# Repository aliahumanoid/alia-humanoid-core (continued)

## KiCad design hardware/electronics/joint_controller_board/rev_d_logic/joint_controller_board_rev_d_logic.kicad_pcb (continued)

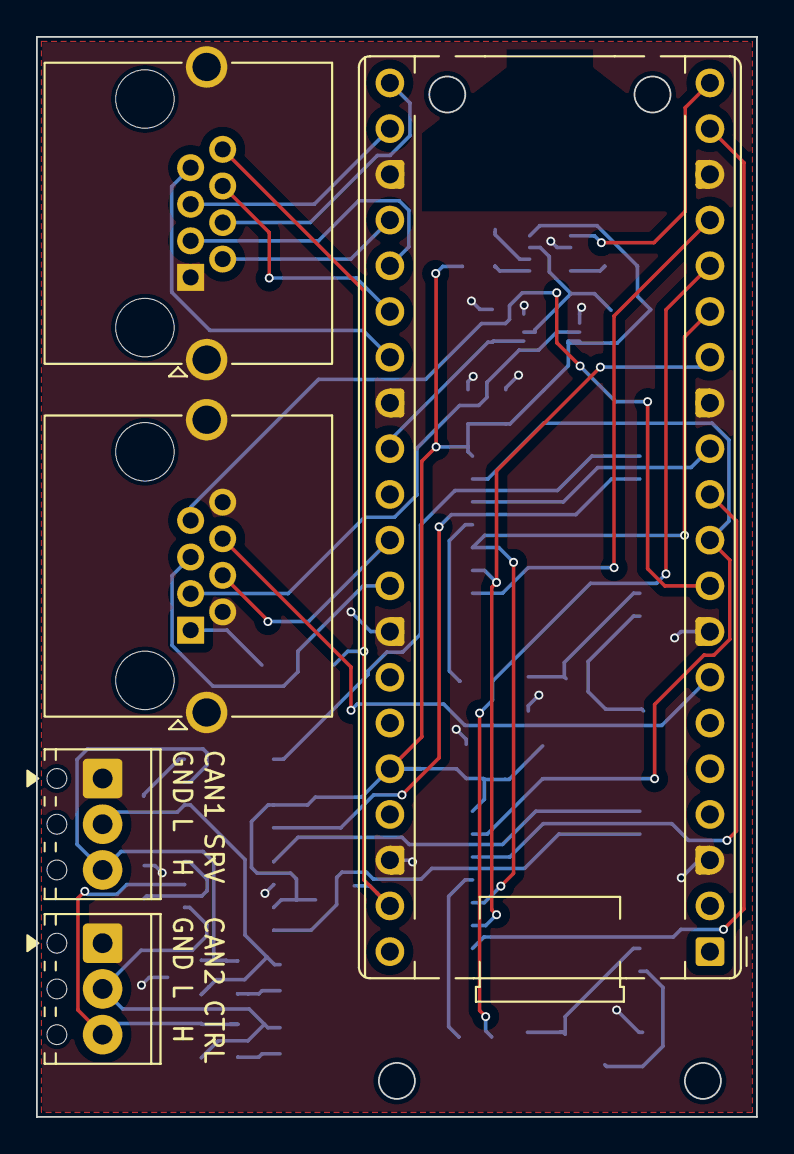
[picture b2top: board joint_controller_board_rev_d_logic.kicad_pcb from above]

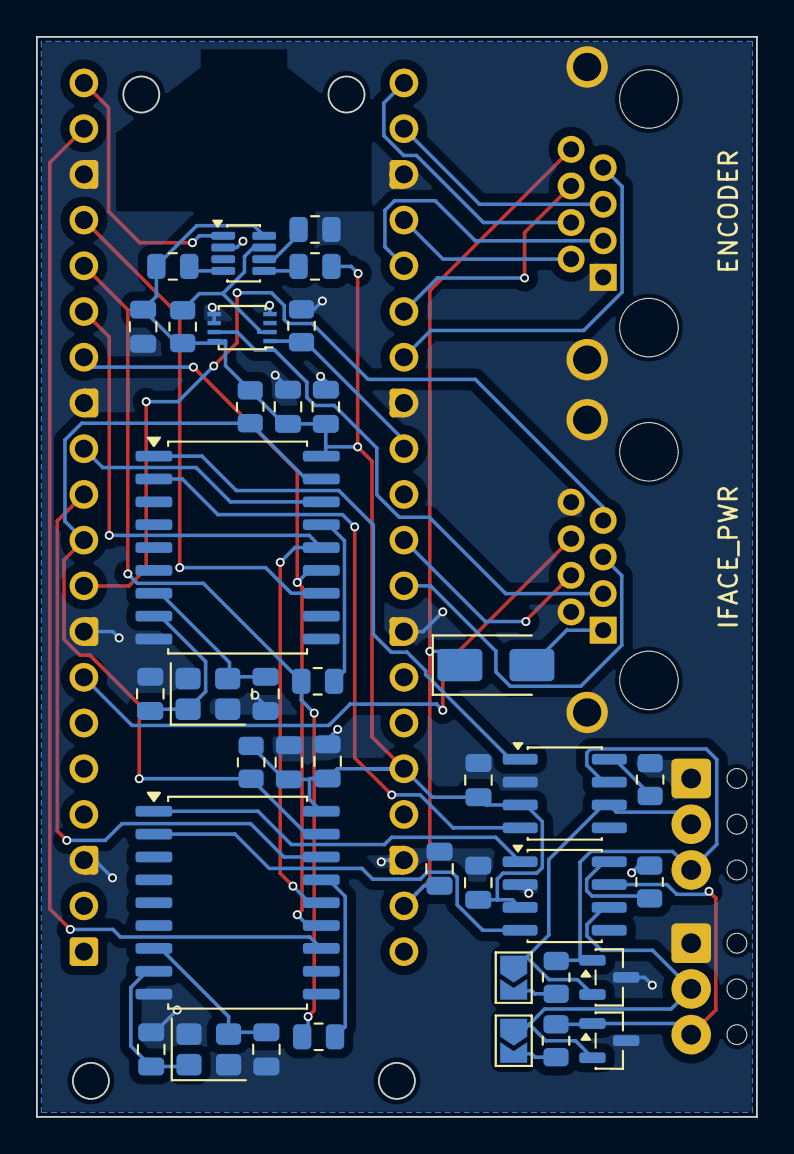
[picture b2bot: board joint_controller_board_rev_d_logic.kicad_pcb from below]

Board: 2 copper layers, 40.0 x 60.0 mm, 43 parts (38 on the bottom side), 47 nets.

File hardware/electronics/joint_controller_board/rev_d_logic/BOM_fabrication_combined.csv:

Designator,Footprint,Quantity,Manufacturer Part Number,Manufacturer,Description,Assembly_Type,Populate,Sourcing,Notes
U_CAN1,SOIC-18W_7.5x11.6mm_P1.27mm,1,MCP2515-E/SO,Microchip,Stand-alone CAN controller with SPI interface,SMD,YES,LCSC / preferred source,CAN1 controller
U_CAN2,SOIC-18W_7.5x11.6mm_P1.27mm,1,MCP2515-E/SO,Microchip,Stand-alone CAN controller with SPI interface,SMD,YES,LCSC / preferred source,CAN2 controller
U_TRX1,SOIC-8_3.9x4.9mm_P1.27mm,1,SN65HVD230DR,Texas Instruments,3.3V CAN transceiver,SMD,YES,LCSC / preferred source,CAN1 transceiver
U_TRX2,SOIC-8_3.9x4.9mm_P1.27mm,1,SN65HVD230DR,Texas Instruments,3.3V CAN transceiver,SMD,YES,LCSC / preferred source,CAN2 transceiver
U_WDT1,SOT-23-8,1,MAX6369KA+T,Analog Devices / Maxim,Pin-selectable watchdog timer,SMD,YES,LCSC / preferred source,Hardware watchdog
U4,VSSOP-8_2.4x2.1mm_P0.5mm,1,SN74LVC2G08DCUR,Texas Instruments,Dual AND gate 1.65V to 5.5V,SMD,YES,LCSC / preferred source,Safety gating logic
D1,SOT-23,1,PESD2CAN24XLT-Q,Nexperia,Automotive CAN ESD protection diode,SMD,YES,LCSC / preferred source,CAN1 TVS
D2,SOT-23,1,PESD2CAN24XLT-Q,Nexperia,Automotive CAN ESD protection diode,SMD,YES,LCSC / preferred source,CAN2 TVS
D_PWR1,D_SMA,1,SS24,Multiple,Schottky diode 2A 40V SMA,SMD,YES,LCSC / preferred source,5V input OR-ing / reverse backfeed protection
Y1,Crystal_SMD_3225-4Pin_3.2x2.5mm,1,3225 8M 12PF 10PPM,SOSET / Equivalent,8MHz SMD crystal 3225-4P,SMD,YES,LCSC / preferred source,CAN1 clock crystal
Y2,Crystal_SMD_3225-4Pin_3.2x2.5mm,1,3225 8M 12PF 10PPM,SOSET / Equivalent,8MHz SMD crystal 3225-4P,SMD,YES,LCSC / preferred source,CAN2 clock crystal
C2,C_0805_2012Metric,1,CL21B104KBCNNNC,Samsung,100nF 50V X7R 0805 capacitor,SMD,YES,LCSC / preferred source,Decoupling
C6,C_0805_2012Metric,1,CL21B104KBCNNNC,Samsung,100nF 50V X7R 0805 capacitor,SMD,YES,LCSC / preferred source,Decoupling
C_CAN1_VDD1,C_0805_2012Metric,1,CL21B104KBCNNNC,Samsung,100nF 50V X7R 0805 capacitor,SMD,YES,LCSC / preferred source,CAN1 MCP decoupling
C_CAN1_TRX1,C_0805_2012Metric,1,CL21B104KBCNNNC,Samsung,100nF 50V X7R 0805 capacitor,SMD,YES,LCSC / preferred source,CAN1 transceiver decoupling
C_CAN2_VDD2,C_0805_2012Metric,1,CL21B104KBCNNNC,Samsung,100nF 50V X7R 0805 capacitor,SMD,YES,LCSC / preferred source,CAN2 MCP decoupling
C_CAN2_TRX2,C_0805_2012Metric,1,CL21B104KBCNNNC,Samsung,100nF 50V X7R 0805 capacitor,SMD,YES,LCSC / preferred source,CAN2 transceiver decoupling
C_CAN1_BULK1,C_0805_2012Metric,1,CL21A105KBQNNNE,Samsung,1uF 50V X5R 0805 capacitor,SMD,YES,LCSC / preferred source,CAN1 local bulk
C_CAN2_BULK2,C_0805_2012Metric,1,CL21A105KBQNNNE,Samsung,1uF 50V X5R 0805 capacitor,SMD,YES,LCSC / preferred source,CAN2 local bulk
C_CAN1_OSC1,C_0805_2012Metric,1,CL21C180JBANNNC,Samsung,18pF C0G 50V 0805 capacitor,SMD,YES,LCSC / preferred source,CAN1 crystal load
C_CAN1_OSC2,C_0805_2012Metric,1,CL21C180JBANNNC,Samsung,18pF C0G 50V 0805 capacitor,SMD,YES,LCSC / preferred source,CAN1 crystal load
C_CAN2_OSC3,C_0805_2012Metric,1,CL21C180JBANNNC,Samsung,18pF C0G 50V 0805 capacitor,SMD,YES,LCSC / preferred source,CAN2 crystal load
C_CAN2_OSC4,C_0805_2012Metric,1,CL21C180JBANNNC,Samsung,18pF C0G 50V 0805 capacitor,SMD,YES,LCSC / preferred source,CAN2 crystal load
R1,R_0805_2012Metric,1,RC0805FR-0710KL,Yageo,10k Ohm 1% 0805 resistor,SMD,YES,LCSC / preferred source,Watchdog network
R2,R_0805_2012Metric,1,RC0805FR-0710KL,Yageo,10k Ohm 1% 0805 resistor,SMD,YES,LCSC / preferred source,Watchdog network
R3,R_0805_2012Metric,1,RC0805FR-0710KL,Yageo,10k Ohm 1% 0805 resistor,SMD,YES,LCSC / preferred source,Watchdog network
R4,R_0805_2012Metric,1,RC0805FR-0710KL,Yageo,10k Ohm 1% 0805 resistor,SMD,YES,LCSC / preferred source,Watchdog network
R5,R_0805_2012Metric,1,RC0805FR-0710KL,Yageo,10k Ohm 1% 0805 resistor,SMD,YES,LCSC / preferred source,Watchdog network
R_CAN1_RST1,R_0805_2012Metric,1,RC0805FR-0710KL,Yageo,10k Ohm 1% 0805 resistor,SMD,YES,LCSC / preferred source,CAN1 reset pull-up
R_CAN2_RST2,R_0805_2012Metric,1,RC0805FR-0710KL,Yageo,10k Ohm 1% 0805 resistor,SMD,YES,LCSC / preferred source,CAN2 reset pull-up
R_CAN1_RS1,R_0805_2012Metric,1,RC0805JR-070RL,Yageo,0 Ohm 0805 jumper resistor,SMD,YES,LCSC / preferred source,CAN1 RS strap
R_CAN2_RS2,R_0805_2012Metric,1,RC0805JR-070RL,Yageo,0 Ohm 0805 jumper resistor,SMD,YES,LCSC / preferred source,CAN2 RS strap
R_SO_SPI1,R_0805_2012Metric,1,RC0805FR-0722RL,Yageo,22 Ohm 1% 0805 resistor,SMD,YES,LCSC / preferred source,SPI SO damping
R_SO_SPI2,R_0805_2012Metric,1,RC0805FR-0722RL,Yageo,22 Ohm 1% 0805 resistor,SMD,YES,LCSC / preferred source,SPI SO damping
R_TERM_CAN1,R_0805_2012Metric,1,RC0805FR-07120RL,Yageo,120 Ohm 1% 0805 resistor,SMD,YES,LCSC / preferred source,CAN1 termination
R_TERM_CAN2,R_0805_2012Metric,1,RC0805FR-07120RL,Yageo,120 Ohm 1% 0805 resistor,SMD,YES,LCSC / preferred source,CAN2 termination
SJ_TERM_CAN1,SolderJumper-2_P1.3mm_Open_TrianglePad1.0x1.5mm,1,PCB_FEATURE,NA,Solder jumper footprint on PCB,PCB,YES,PCB fabrication only,Do not add as assembled component
SJ_TERM_CAN2,SolderJumper-2_P1.3mm_Open_TrianglePad1.0x1.5mm,1,PCB_FEATURE,NA,Solder jumper footprint on PCB,PCB,YES,PCB fabrication only,Do not add as assembled component
J1,RJ45_Amphenol_RJHSE5380,1,RJHSE5380,Amphenol ICC,RJ45 8P8C right-angle THT connector,THT,YES,Consigned recommended,IFACE connector
J2,RJ45_Amphenol_RJHSE5380,1,RJHSE5380,Amphenol ICC,RJ45 8P8C right-angle THT connector,THT,YES,Consigned recommended,Encoder connector
J_CAN1_IN1,"TerminalBlock_Phoenix_MPT-0,5-3-2.54_1x03_P2.54mm_Horizontal",1,1725669,Phoenix Contact,3-pin pluggable terminal block 2.54mm pitch,THT,YES,LCSC / preferred source,CAN1 connector
J_CAN2_IN2,"TerminalBlock_Phoenix_MPT-0,5-3-2.54_1x03_P2.54mm_Horizontal",1,1725669,Phoenix Contact,3-pin pluggable terminal block 2.54mm pitch,THT,YES,LCSC / preferred source,CAN2 connector
U1,RaspberryPi_Pico_Common_THT,2,PPTC201LFBN-RC,Sullins / Equivalent,Female socket strip 1x20 2.54mm THT,THT,YES,Consigned or equivalent,ASSEMBLE ONLY 2x female socket strips on U1 footprint; DO NOT PLACE Raspberry Pi Pico module (customer supplied, plug-in after delivery)

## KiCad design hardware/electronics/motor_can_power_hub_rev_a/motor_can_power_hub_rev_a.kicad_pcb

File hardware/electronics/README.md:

# Alia Humanoid Electronics

**Status:** Public release scoped to the current controller logic board and two passive hubs  
**License:** CC BY-NC-ND 4.0 (Phase 0) → See [hardware/LICENSE.md](../LICENSE.md)

---

## Overview

This directory contains the electronics currently exposed in the public repository. Older controller revisions and internal support files are intentionally excluded from publication.

## Published Boards

### `joint_controller_board/rev_d_logic`

Main RP2350 logic/control board for one joint.

- RP2350 Pico 2 host module
- Two onboard CAN channels (`MCP2515 + SN65HVD230`)
- RJ45 interface for encoder and power/safety breakout
- KiCad source, BOM, and current fabrication package

### `MT6835_hub_rev_a`

Passive encoder hub that fans out up to three MT6835 SPI encoders into the RJ45 encoder port used by `rev_d_logic`.

- KiCad source
- BOM
- Current fabrication package

### `motor_can_power_hub_rev_a`

Passive CAN/power distribution board for motor wiring.

- XT60 power input
- CAN input terminal block
- Five motor harness outputs
- KiCad source, BOM, and current fabrication package

## Directory Structure

```text
electronics/
├── joint_controller_board/
│   └── rev_d_logic/
├── MT6835_hub_rev_a/
└── motor_can_power_hub_rev_a/
```

---

**Questions?** Contact us at info@aliahumanoid.com

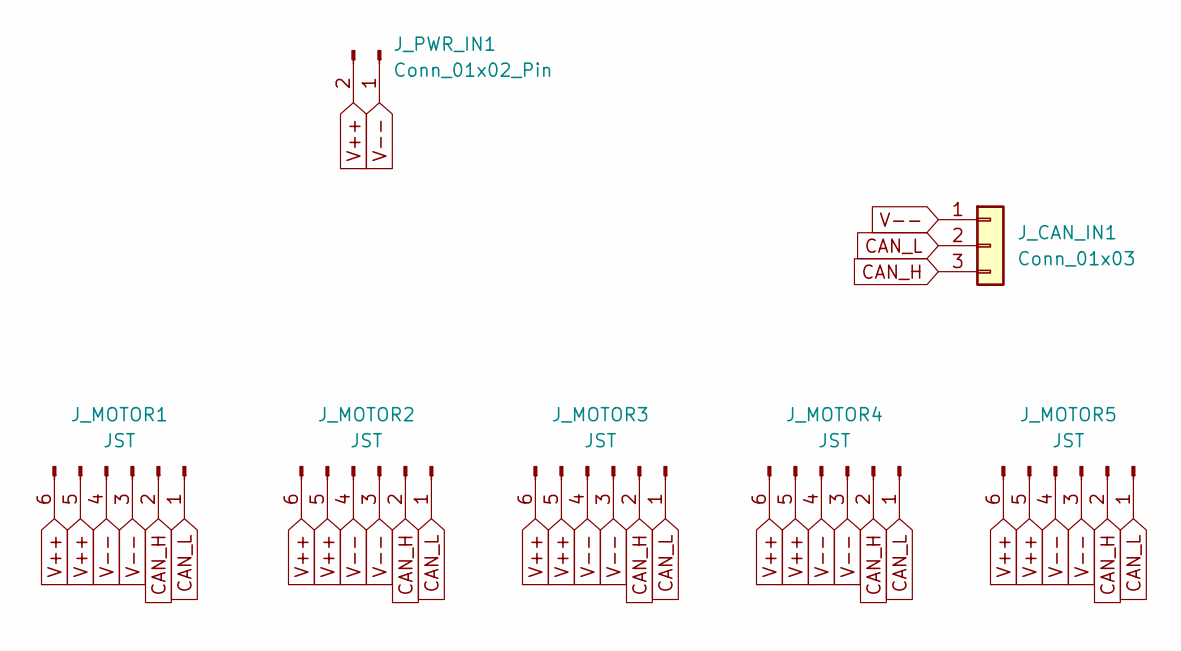
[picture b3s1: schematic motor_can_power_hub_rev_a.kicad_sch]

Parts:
J_CAN_IN1: Conn_01x03; TerminalBlock_Phoenix_MPT-0,5-3-2.54_1x03_P2.54mm_Horizontal
J_MOTOR1, J_MOTOR2, J_MOTOR3, J_MOTOR4, J_MOTOR5: JST; JST_ZH_B6B-ZR_1x06_P1.50mm_Vertical
J_PWR_IN1: Conn_01x02_Pin; AMASS_XT60PW-M_1x02_P7.20mm_Horizontal

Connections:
CAN_H: J_CAN_IN1.3, J_MOTOR1.2, J_MOTOR2.2, J_MOTOR3.2, J_MOTOR4.2, J_MOTOR5.2
CAN_L: J_CAN_IN1.2, J_MOTOR1.1, J_MOTOR2.1, J_MOTOR3.1, J_MOTOR4.1, J_MOTOR5.1
V++: J_MOTOR1.5, J_MOTOR1.6, J_MOTOR2.5, J_MOTOR2.6, J_MOTOR3.5, J_MOTOR3.6, J_MOTOR4.5, J_MOTOR4.6, J_MOTOR5.5, J_MOTOR5.6, J_PWR_IN1.2
V--: J_CAN_IN1.1, J_MOTOR1.3, J_MOTOR1.4, J_MOTOR2.3, J_MOTOR2.4, J_MOTOR3.3, J_MOTOR3.4, J_MOTOR4.3, J_MOTOR4.4, J_MOTOR5.3, J_MOTOR5.4, J_PWR_IN1.1

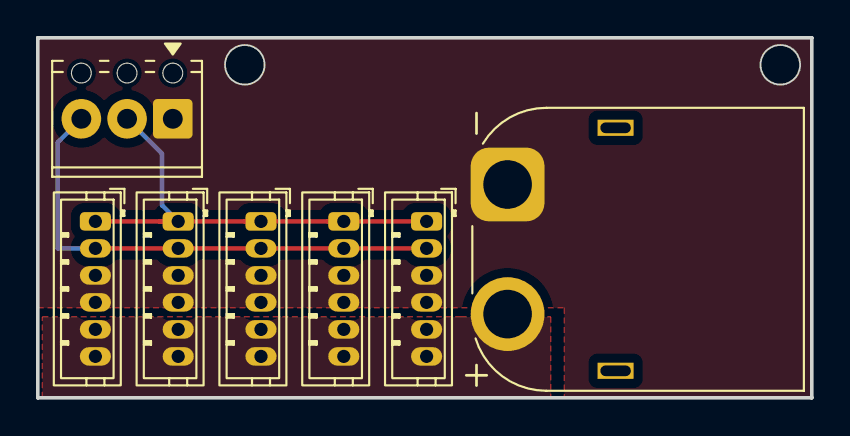
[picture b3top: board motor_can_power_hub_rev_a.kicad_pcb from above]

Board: 2 copper layers, 43.0 x 20.0 mm, 7 parts (0 on the bottom side), 4 nets.

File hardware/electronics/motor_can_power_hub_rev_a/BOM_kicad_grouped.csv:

"Designator","Value","Footprint","Datasheet","Description","Qty","DNP"
"J_CAN_IN1","Conn_01x03","TerminalBlock_Phoenix:TerminalBlock_Phoenix_MPT-0,5-3-2.54_1x03_P2.54mm_Horizontal","~","Generic connector, single row, 01x03, script generated (kicad-library-utils/schlib/autogen/connector/)","1",""
"J_MOTOR1-J_MOTOR5","JST","Connector_JST:JST_ZH_B6B-ZR_1x06_P1.50mm_Vertical","~","Generic connector, single row, 01x06, script generated","5",""
"J_PWR_IN1","Conn_01x02_Pin","Connector_AMASS:AMASS_XT60PW-M_1x02_P7.20mm_Horizontal","~","Generic connector, single row, 01x02, script generated","1",""

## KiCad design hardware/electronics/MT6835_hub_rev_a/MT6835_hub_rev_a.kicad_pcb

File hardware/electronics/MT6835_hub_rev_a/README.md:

# MT6835 Hub Rev A

Passive breakout board that routes up to three MT6835 SPI encoder modules into the RJ45 encoder port used by `joint_controller_board/rev_d_logic` (`J2`).

## Purpose

- Aggregate three encoder channels into one RJ45 link
- Preserve the SPI pin mapping expected by the controller board
- Keep the hub fully passive: no active components, only connector routing

## RJ45 Output Pinout

This connector maps directly to `rev_d_logic` encoder connector `J2`.

1. `GND`
2. `SCK`
3. `MOSI`
4. `MISO`
5. `CS1`
6. `CS2`
7. `CS3`
8. `+5V`

## Encoder Input Connectors (`J1/J2/J3`)

Each encoder connector is a 6-pin SPI header:

1. `GND`
2. `CSx`
3. `SCK`
4. `MOSI`
5. `MISO`
6. `+5V`

## Connector Family

The board uses 1.25 mm PicoBlade connectors for the encoder side.

- PCB footprint: `Molex_PicoBlade_53398-0671_1x06-1MP_P1.25mm_Vertical`
- Board header: `Molex 53398-0671`
- Matching cable housing: `Molex 51021-0600`
- Matching crimp terminal: `Molex 50079-8100`

## Verification Status

Latest checks on the current board revision:

- ERC: 0 violations
- DRC: 0 violations
- Unconnected pads: 0
- Schematic/PCB parity: 0 issues

## Included Files

- `MT6835_hub_rev_a.kicad_sch`
- `MT6835_hub_rev_a.kicad_pcb`
- `MT6835_hub_rev_a.kicad_pro`
- `MT6835_hub_rev_a.step`
- `BOM_fabrication.csv`
- `BOM_kicad_grouped.csv`
- `fabrication_release_2026-02-27_fix_drill/MT6835_hub_rev_a_fabrication_release_2026-02-27_fix_drill.zip`

## Notes

- This board carries only connector routing and power distribution for SPI encoder lines.
- The `fix_drill` fabrication package is the current release candidate for manufacturing.

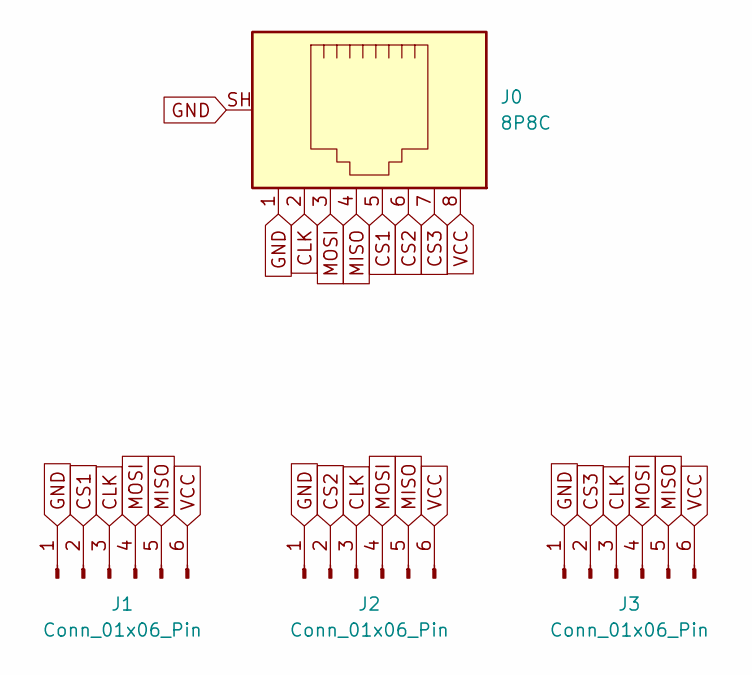
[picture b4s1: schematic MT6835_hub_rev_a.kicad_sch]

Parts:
J0: 8P8C; RJ45_Amphenol_RJHSE5380
J1, J2, J3: Conn_01x06_Pin; Molex_PicoBlade_53398-0671_1x06-1MP_P1.25mm_Vertical

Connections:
CLK: J0.2, J1.3, J2.3, J3.3
CS1: J0.5, J1.2
CS2: J0.6, J2.2
CS3: J0.7, J3.2
GND: J0.1, J0.SH, J1.1, J2.1, J3.1
MISO: J0.4, J1.5, J2.5, J3.5
MOSI: J0.3, J1.4, J2.4, J3.4
VCC: J0.8, J1.6, J2.6, J3.6

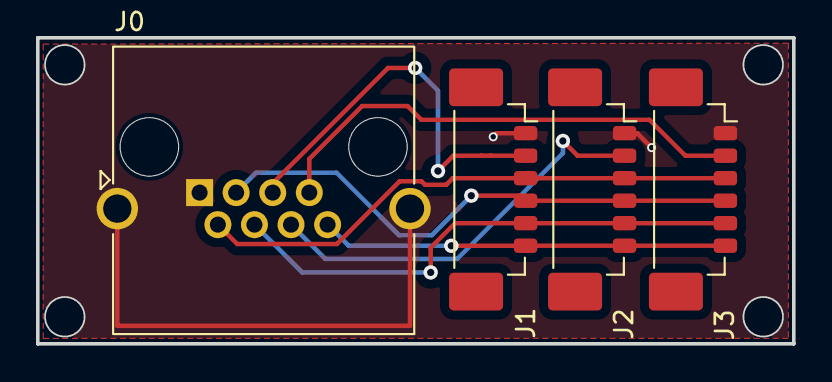
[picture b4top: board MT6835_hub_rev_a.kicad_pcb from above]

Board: 2 copper layers, 42.0 x 17.0 mm, 4 parts (0 on the bottom side), 8 nets.

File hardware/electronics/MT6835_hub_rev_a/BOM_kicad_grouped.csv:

"Designator","Value","Footprint","Datasheet","Description","Qty","DNP"
"J0","8P8C","Connector_RJ:RJ45_Amphenol_RJHSE5380","~","RJ connector, 8P8C (8 positions 8 connected), RJ31/RJ32/RJ33/RJ34/RJ35/RJ41/RJ45/RJ49/RJ61, Shielded","1",""
"J1-J3","Conn_01x06_Pin","Connector_Molex:Molex_PicoBlade_53398-0671_1x06-1MP_P1.25mm_Vertical","~","","3",""

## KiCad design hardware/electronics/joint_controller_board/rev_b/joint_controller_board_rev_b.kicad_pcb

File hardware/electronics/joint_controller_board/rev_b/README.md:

# Joint Controller Board — Revision B

**Status:** ✅ Production Ready (48V-Compatible)  
**Design Tool:** KiCad 8.0  
**PCB Ordered:** December 10, 2025 (Rev B.1)  
**Updated for Assembly:** December 11, 2025 (Rev B.2)  
**Last Updated:** December 2025

---

## Overview

Evolution of Rev A with integrated **Hardware Safety System** for production-grade operation.

**Key Features:**
- ✅ **Safety Power Switch** — 2× MOSFET in parallel for 48V/40A
- ✅ **Hardware Watchdog** — Independent MCU freeze detection
- ✅ **Gate Driver** — Bootstrap high-side MOSFET control
- ✅ **Buck Converter** — 48V → 12V regulated supply
- ✅ **48V Compatible** — Future-proof design (works at 24V too)
- ✅ **2oz Copper** — High-current capable traces

---

## Specifications

| Parameter | Value |
|-----------|-------|
| **Board Size** | 72 × 128 mm |
| **PCB Layers** | 2 |
| **Copper Weight** | 2 oz |
| **Input Voltage** | 24-48V DC (tested) |
| **Max Current** | 40A continuous |
| **Power Loss** | <1W @ 20A (per MOSFET) |
| **Shutoff Time** | <10 µs |
| **Watchdog Timeout** | ~1 second (MAX6369KA) |

---

## Safety System Architecture

```
                    ┌─────────────┐
    48V IN ────────►│   FUSE 5A   │
                    └──────┬──────┘
                           │
                    ┌──────▼──────┐
                    │  TVS SMBJ60A │
                    └──────┬──────┘
                           │
              ┌────────────┼────────────┐
              │            │            │
       ┌──────▼──────┐     │     ┌──────▼──────┐
       │  MOSFET Q1  │     │     │  MOSFET Q2  │
       │  IRFB4110   │     │     │  IRFB4110   │
       └──────┬──────┘     │     └──────┬──────┘
              │            │            │
              └────────────┼────────────┘
                           │
                    48V OUT TO MOTORS
```

### Safety Logic

```
MOTOR_POWER = SAFETY_ENABLE (GP22) AND NOT(WATCHDOG_TIMEOUT)
```

| Condition | SAFETY_ENABLE | Watchdog | Motor Power |
|-----------|---------------|----------|-------------|
| Normal Operation | HIGH | Kicked | ✅ ON |
| Software Disable | LOW | Kicked | ❌ OFF |
| MCU Freeze | HIGH/LOW | Timeout | ❌ OFF |
| Emergency Stop | LOW | - | ❌ OFF |

---

## GPIO Assignments

| GPIO | Function | Direction | Description |
|------|----------|-----------|-------------|
| **GP15** | Watchdog Kick (WDI) | OUTPUT | Pulse to reset watchdog timer |
| **GP22** | Safety Enable | OUTPUT | HIGH = Enable power to motors |

---

## Bill of Materials (BOM)

### Active Components

| Ref | Description | Part Number | Digi-Key | Qty |
|-----|-------------|-------------|----------|-----|
| U_WDT1 | Watchdog Timer | MAX6369KA+T | MAX6369KA+TCT-ND | 1 |
| U_DRV1 | Gate Driver | UCC27282DR | 296-UCC27282DRCT-ND | 1 |
| U4 | AND Gate | SN74LVC2G08DCUR | 296-13264-1-ND | 1 |
| U2 | Buck Converter 60V | **LM2576HVT-12/LF03** | 296-41559-5-ND | 1 |
| Q1, Q2 | Power MOSFET | IRFB4110PBF | 448-IRFB4110PBF-ND | 2 |

### Passive Components

| Ref | Description | Value | Digi-Key | Qty |
|-----|-------------|-------|----------|-----|
| R1-R5 | Resistor 0805 | 10kΩ | RR12P10.0KDCT-ND | 5 |
| R6 | Resistor 0805 | 10Ω | RHM10KCT-ND | 1 |
| C1 | Electrolytic Radial Ø10mm | **220µF 63V** | (Amazon/generic) | 1 |
| C2, C5, C6 | Ceramic 0805 | 100nF 50V | CL21B104KBCNNNC | 3 |
| C3 | Ceramic 0805 | 1µF 25V (bootstrap) | CL21B105KAFNNNE | 1 |
| C4 | Electrolytic Radial Ø10mm | **100µF 63V** | 1189-4028-ND | 1 |
| L1 | Inductor THT | 33µH 3.6A | 732-3415-ND | 1 |

### Protection & Power

| Ref | Description | Part Number | Digi-Key | Qty |
|-----|-------------|-------------|----------|-----|
| D1 | Schottky Diode (Pico) | 1N5817 | (in stock) | 1 |
| D2 | TVS Diode | SMBJ60A | SMBJ60AFSCT-ND | 1 |
| D3 | Schottky Diode (Buck) | SS14 | SS14CT-ND | 1 |
| F1 | Fuse Holder | Keystone 3568 | 36-3568-ND | 1 |
| - | Fuse 5A 80V | Littelfuse 166.7000.4502 | F5156-ND | 1+ |

### Connectors

| Ref | Description | Source | Qty |
|-----|-------------|--------|-----|
| J1 | Terminal Block 2-pin 5.08mm | (in stock) | 1 |
| J2, J3 | XT60PW PCB 90° | Amazon | 2 |

---

## Order Information

### PCBWay Order (Dec 10, 2025)

| Parameter | Value |
|-----------|-------|
| Quantity | 5 pcs |
| Layers | 2 |
| Thickness | 1.6mm |
| Copper | **2 oz** |
| Surface Finish | HASL Lead-Free |
| Solder Mask | Green |
| Silkscreen | White |
| Build Time | Express 48h |
| Price | $82.89 USD |

### Digi-Key Order (Dec 10, 2025)

All active/passive components ordered. ~205€ total.

### Amazon Order (Dec 10, 2025)

- XT60 connectors (PCB mount + cable type)
- ~55€ total

---

## Files

| File | Description |
|------|-------------|
| `joint_controller_board_rev_b.kicad_pro` | KiCad project |
| `joint_controller_board_rev_b.kicad_sch` | Schematic |
| `joint_controller_board_rev_b.kicad_pcb` | PCB layout |
| `joint_controller_rev_b.zip` | Gerber files for manufacturing |

---

## Assembly Notes

### Soldering Order (Recommended)

1. **SMD Components First** (reflow or hand solder)
   - R1-R6 (0805 resistors)
   - C2, C3, C5, C6 (0805 capacitors)
   - U4 (VSSOP-8 AND gate)
   - U_WDT1 (SOT23-8 watchdog)
   - U_DRV1 (SOIC-8 gate driver)
   - D2 (SMD TVS)
   - D3 (SMD Schottky)

2. **Through-Hole Components**
   - C1, C4 (electrolytic capacitors - watch polarity!)
   - L1 (inductor)
   - Q1, Q2 (MOSFETs - ensure proper orientation)
   - U2 (LM2576HVT-12 buck converter - check pinout)
   - F1 (fuse holder)
   - J1 (terminal block)

3. **Connectors Last**
   - J2, J3 (XT60 - verify polarity with silkscreen)
   - Pico module (if socket-mounted)

### Important Warnings

⚠️ **POLARITY** — Check electrolytic capacitors and XT60 connectors!

⚠️ **MOSFET ORIENTATION** — Gate, Drain, Source must match schematic!

⚠️ **THERMAL** — Q1, Q2, and LM2576HV may need heatsinks at high current.

---

## Testing Procedure

### 1. Visual Inspection
- [ ] No solder bridges
- [ ] All components placed correctly
- [ ] Polarity correct on capacitors

### 2. Continuity Tests (No Power)
- [ ] GND net continuous
- [ ] No shorts between power rails
- [ ] XT60 polarity matches silkscreen

### 3. Power-On Test (5V only first)
- [ ] Apply 5V to Pico via USB
- [ ] Measure 3.3V rail
- [ ] Verify watchdog LED/status

### 4. Full Power Test (48V)
- [ ] Connect 48V with current-limited PSU (1A max)
- [ ] Measure 12V rail from LM2576HV
- [ ] Test safety enable/disable
- [ ] Verify watchdog timeout behavior

---

## Firmware Integration

Add to Pico firmware:

```cpp
// Safety System GPIO
#define PIN_SAFETY_ENABLE  22
#define PIN_WATCHDOG_KICK  15

void safety_init() {
    pinMode(PIN_SAFETY_ENABLE, OUTPUT);
    pinMode(PIN_WATCHDOG_KICK, OUTPUT);
    digitalWrite(PIN_SAFETY_ENABLE, LOW);  // Start disabled
}

void safety_enable() {
    digitalWrite(PIN_SAFETY_ENABLE, HIGH);
}

void safety_disable() {
    digitalWrite(PIN_SAFETY_ENABLE, LOW);
}

void watchdog_kick() {
    // Toggle WDI pin to reset watchdog
    digitalWrite(PIN_WATCHDOG_KICK, HIGH);
    delayMicroseconds(1);
    digitalWrite(PIN_WATCHDOG_KICK, LOW);
}

// Call watchdog_kick() in main loop at least every 500ms
```

---

## Changelog

### Rev B.3 (December 2025)
- **U4:** Fixed footprint VSSOP-8_3.0x3.0mm_P0.65mm → VSSOP-8_2.4x2.1mm_P0.5mm
  - TI DCU package has 0.5mm pitch, not 0.65mm
  - Discovered during PCBWay assembly (component didn't fit pads)

### Rev B.2 (December 2025)
- **U_BUCK:** LM2596T-12 → LM2576HVT-12 (60V input for 48V operation)
- **C1:** 220µF 25V → 220µF 63V with larger footprint (Ø10mm)
- **D2:** Corrected TVS diode orientation (cathode to +48V)
- Prepared for PCBWay PCBA with turnkey components

### Rev B.1 (December 2025)
- Initial Rev B production order
- Fixed footprints: U_DRV1 (SOIC-8), U_WDT1 (SOT23-8), U4 (VSSOP-8)

### Rev B (December 2025)
- Added hardware safety system
- Added buck converter for gate driver supply
- Added watchdog timer
- Upgraded to 2oz copper for power traces
- Added TVS protection on 48V input

### Rev A (November 2025)
- Initial design
- Basic CAN controller functionality
- Pico 2 integration

---

## License

Hardware design licensed under **CC BY-NC-ND 4.0** (Phase 0)

See [hardware/LICENSE.md](../../LICENSE.md) for full licensing roadmap.

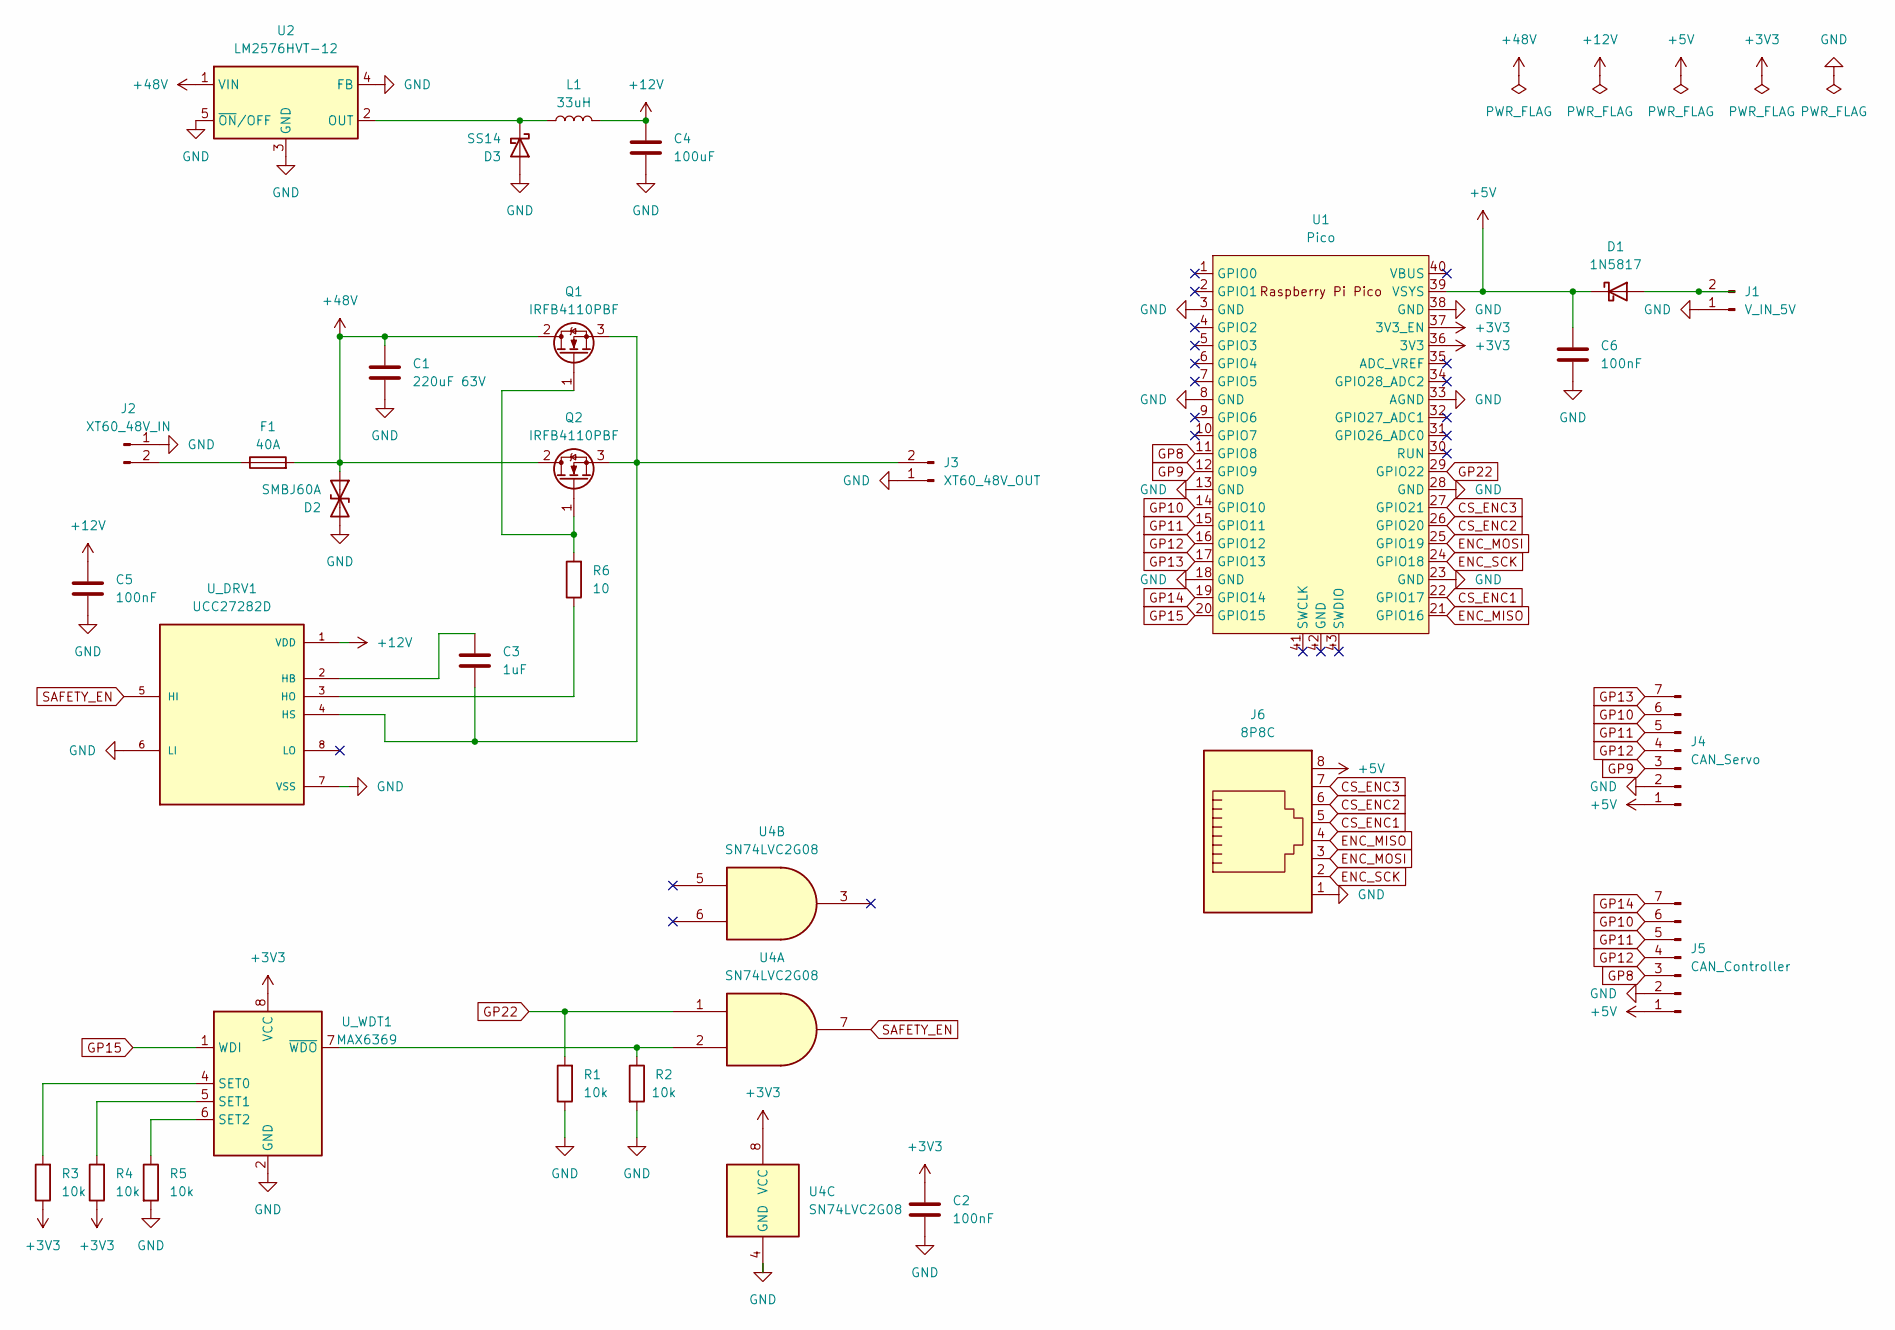
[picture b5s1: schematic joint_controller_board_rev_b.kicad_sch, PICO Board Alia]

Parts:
C1: 220uF 63V; CP_Radial_D10.0mm_P5.00mm
C2, C5, C6: 100nF; C_0805_2012Metric
C3: 1uF; C_0805_2012Metric
C4: 100uF; CP_Radial_D10.0mm_P5.00mm
D1: 1N5817; D_DO-41_SOD81_P10.16mm_Horizontal
D2: SMBJ60A; D_SMB
D3: SS14; D_SMA
F1: 40A; Fuseholder_Blade_ATO_Littelfuse_Pudenz_2_Pin
J1: V_IN_5V; TerminalBlock_bornier-2_P5.08mm
J2: XT60_48V_IN; AMASS_XT60PW-M_1x02_P7.20mm_Horizontal
J3: XT60_48V_OUT; AMASS_XT60PW-F_1x02_P7.20mm_Horizontal
J4: CAN_Servo; PinSocket_1x07_P2.54mm_Vertical
J5: CAN_Controller; PinSocket_1x07_P2.54mm_Vertical
J6: 8P8C; RJ45_Amphenol_RJHSE5380
L1: 33uH; L_Radial_D12.0mm_P5.00mm_Fastron_11P
Q1, Q2: IRFB4110PBF; TO-220-3_Vertical
R1, R2, R3, R4, R5: 10k; R_0805_2012Metric
R6: 10; R_0805_2012Metric
U1: Pico; RPi_Pico_SMD_TH
U2: LM2576HVT-12; TO-220-5_P3.4x3.7mm_StaggerOdd_Lead3.8mm_Vertical
U4: SN74LVC2G08; VSSOP-8_2.4x2.1mm_P0.5mm
U_DRV1: UCC27282D; SOIC-8_3.9x4.9mm_P1.27mm; PARTREV A
U_WDT1: MAX6369; SOT-23-8

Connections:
+3V3: C2.1, R3.1, R4.1, U1.36 (3V3), U1.37 (3V3_EN), U4.8 (VCC), U_WDT1.8 (VCC)
+5V: C6.1, D1.1 (K), J4.1, J5.1, J6.8, U1.39 (VSYS)
+12V: C4.1, C5.1, L1.2, U_DRV1.1 (VDD)
+48V: C1.1, D2.1 (A1), F1.2, Q1.2 (D), Q2.2 (D), U2.1 (VIN)
CS_ENC1: J6.5, U1.22 (GPIO17)
CS_ENC2: J6.6, U1.26 (GPIO20)
CS_ENC3: J6.7, U1.27 (GPIO21)
ENC_MISO: J6.4, U1.21 (GPIO16)
ENC_MOSI: J6.3, U1.25 (GPIO19)
ENC_SCK: J6.2, U1.24 (GPIO18)
GND: C1.2, C2.2, C4.2, C5.2, C6.2, D2.2 (A2), D3.2 (A), J1.1, J2.1, J3.1, J4.2, J5.2, J6.1, R1.1, R2.2, R5.2, U1.3 (GND), U1.8 (GND), U1.13 (GND), U1.18 (GND), U1.23 (GND), U1.28 (GND), U1.33 (AGND), U1.38 (GND), U2.3 (GND), U2.4 (FB), U2.5 (~ON/OFF), U4.4 (GND), U_DRV1.6 (LI), U_DRV1.7 (VSS), U_WDT1.2 (GND)
GP8: J5.3, U1.11 (GPIO8)
GP9: J4.3, U1.12 (GPIO9)
GP10: J4.6, J5.6, U1.14 (GPIO10)
GP11: J4.5, J5.5, U1.15 (GPIO11)
GP12: J4.4, J5.4, U1.16 (GPIO12)
GP13: J4.7, U1.17 (GPIO13)
GP14: J5.7, U1.19 (GPIO14)
GP15: U1.20 (GPIO15), U_WDT1.1 (WDI)
GP22: R1.2, U1.29 (GPIO22), U4.1
unnamed: D1.2 (A), J1.2
unnamed: D3.1 (K), L1.1, U2.2 (OUT)
unnamed: F1.1, J2.2
unnamed: C3.2, J3.2, Q1.3 (S), Q2.3 (S), U_DRV1.4 (HS)
unnamed: Q1.1 (G), Q2.1 (G), R6.2
unnamed: C3.1, U_DRV1.2 (HB)
unnamed: R6.1, U_DRV1.3 (HO)
unnamed: R3.2, U_WDT1.4 (SET0)
unnamed: R4.2, U_WDT1.5 (SET1)
unnamed: R5.1, U_WDT1.6 (SET2)
unnamed: R2.1, U4.2, U_WDT1.7 (~WDO)
SAFETY_EN: U4.7, U_DRV1.5 (HI)

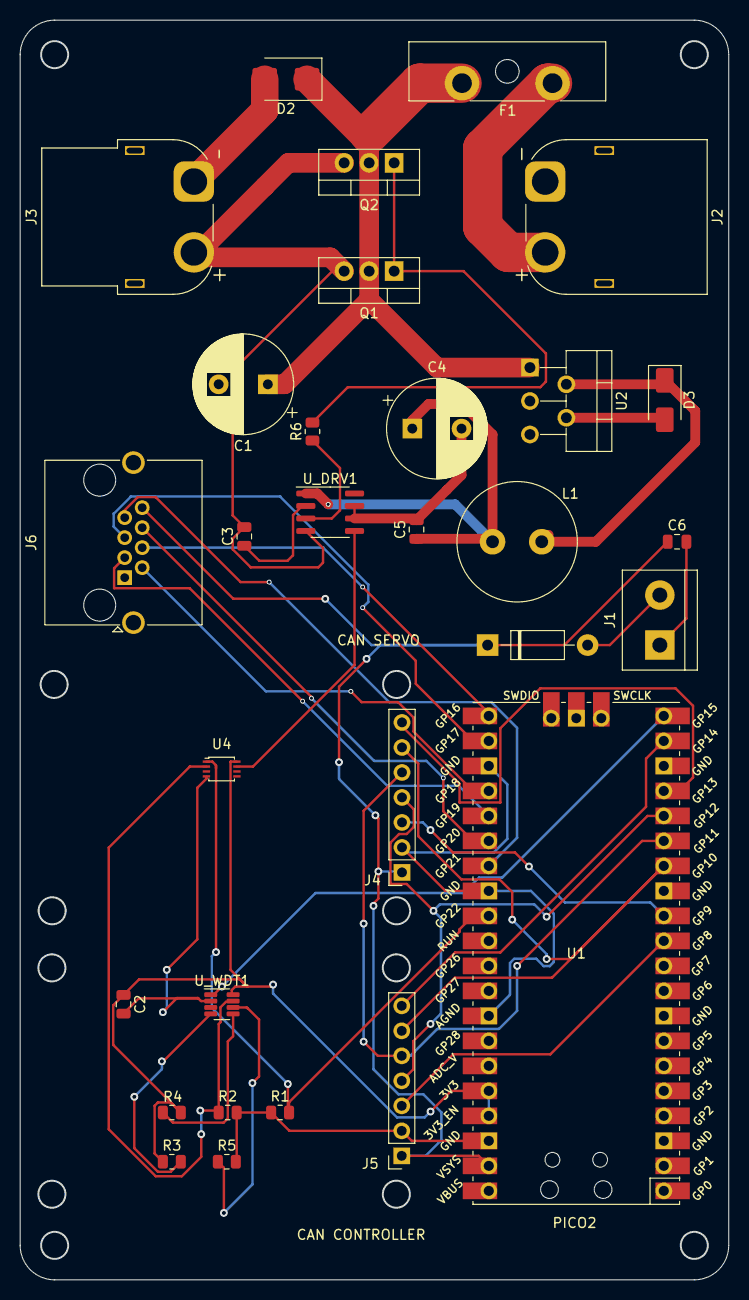
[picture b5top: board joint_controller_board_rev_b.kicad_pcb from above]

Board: 2 copper layers, 72.0 x 128.0 mm, 30 parts (0 on the bottom side), 32 nets.

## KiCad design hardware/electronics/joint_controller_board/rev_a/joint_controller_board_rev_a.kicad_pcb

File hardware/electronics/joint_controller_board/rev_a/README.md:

# Joint Controller Board — Revision A

**Status:** Released  
**Design Tool:** KiCad 7.0+  
**Last Updated:** January 2025

---

## Overview

Dual Raspberry Pi Pico control board for joint actuation and sensor management. Supports both RP2040 and RP2350 microcontrollers.

**Key Features:**
- **Dual Pico slots:** Independent control (Core 0: motor PID, Core 1: communication)
- **MT6835 encoder interface:** High-precision magnetic angle sensors (SPI)
- **Motor driver support:** Compatible with LKM MG4005/MG5010 motors
- **Compact design:** Fits human-scale lower leg assembly

---

## Files Included

### Gerber Files (gerber/)
Manufacturing-ready files for PCB production:
- Copper layers: `*-F_Cu.gbr`, `*-B_Cu.gbr`
- Solder mask: `*-F_Mask.gbr`, `*-B_Mask.gbr`
- Silkscreen: `*-F_Silkscreen.gbr`, `*-B_Silkscreen.gbr`
- Solder paste: `*-F_Paste.gbr`, `*-B_Paste.gbr`
- Edge cuts: `*-Edge_Cuts.gbr`
- Drill files: `*-PTH.drl`, `*-NPTH.drl`
- Job file: `*-job.gbrjob`

**Manufacturing specs:**
- Layers: 2 (double-sided)
- PCB thickness: 1.6mm
- Min track/space: 0.15mm / 0.15mm
- Min hole size: 0.3mm

### KiCad Source Files
- `joint_controller_board_rev_a.kicad_pro` — Project file
- `joint_controller_board_rev_a.kicad_pcb` — PCB layout
- `joint_controller_board_rev_a.kicad_sch` — Schematic
- `joint_controller_board_rev_a.kicad_prl` — Project local settings

**Requirements:** KiCad 7.0 or newer

---

## Manufacturing

1. Upload Gerber files from `gerber/` directory to your PCB manufacturer (JLCPCB, PCBWay, etc.)
2. Recommended settings:
   - Layers: 2
   - Thickness: 1.6mm
   - Surface finish: HASL or ENIG
   - Copper weight: 1oz (35μm)

---

## Assembly Notes

- Solder Pico headers first (through-hole)
- MT6835 encoder connectors require careful alignment
- Test continuity before powering up

**Schematic:** Open `joint_controller_board_rev_a.kicad_sch` in KiCad to view the schematic.

---

## Known Issues / Notes

- **Rev A status:** Functional prototype, validated in ankle assembly
- **Future revisions:** May optimize connector placement and power routing
- This is a test/development board — production version will follow in Phase 1

---

## License

Hardware design licensed under **CC BY-NC-ND 4.0** (Phase 0)

See [hardware/LICENSE.md](../../LICENSE.md) for full licensing roadmap.

---

**Questions?** Contact info@aliahumanoid.com

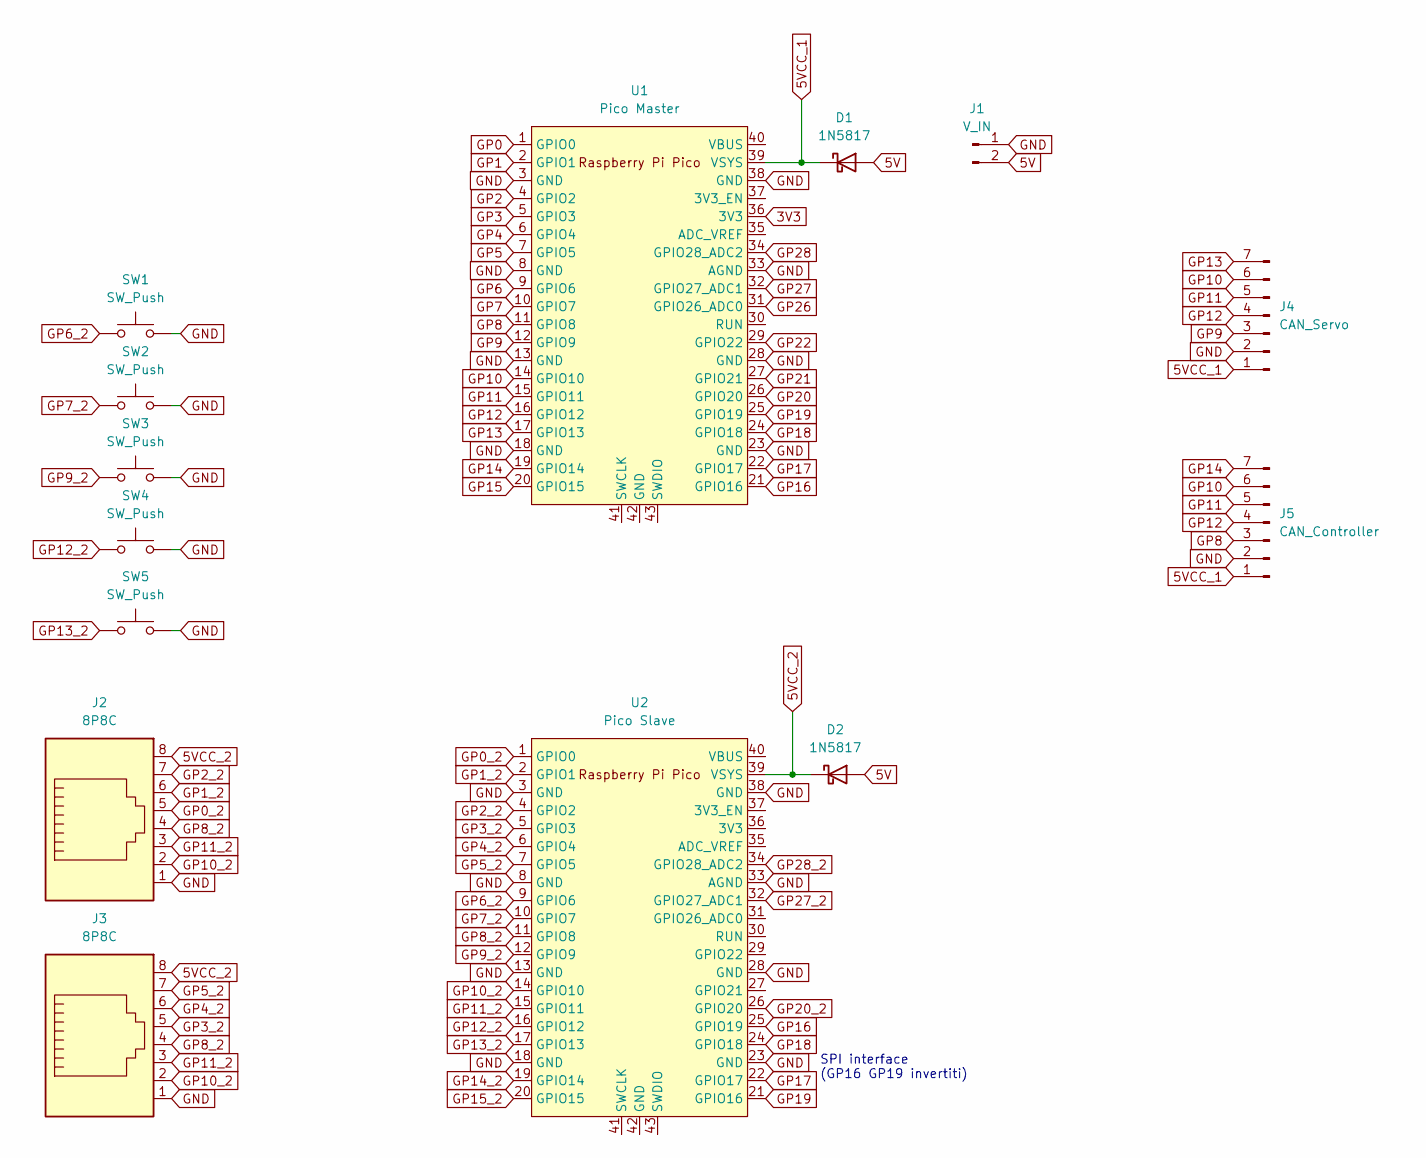
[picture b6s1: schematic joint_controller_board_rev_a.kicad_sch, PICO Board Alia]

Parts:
D1, D2: 1N5817; D_DO-41_SOD81_P10.16mm_Horizontal
J1: V_IN; TerminalBlock_bornier-2_P5.08mm
J2, J3: 8P8C; RJ45_Amphenol_RJHSE5380
J4: CAN_Servo; PinSocket_1x07_P2.54mm_Vertical
J5: CAN_Controller; PinSocket_1x07_P2.54mm_Vertical
SW1, SW2, SW3, SW4, SW5: SW_Push; SW_PUSH_6mm
U1: Pico Master; RPi_Pico_SMD_TH
U2: Pico Slave; RPi_Pico_SMD_TH

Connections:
3V3: U1.36 (3V3)
5V: D1.2 (A), D2.2 (A), J1.2
5VCC_1: D1.1 (K), J4.1, J5.1, U1.39 (VSYS)
5VCC_2: D2.1 (K), J2.8, J3.8, U2.39 (VSYS)
GND: J1.1, J2.1, J3.1, J4.2, J5.2, SW1.2, SW2.2, SW3.2, SW4.2, SW5.2, U1.3 (GND), U1.8 (GND), U1.13 (GND), U1.18 (GND), U1.23 (GND), U1.28 (GND), U1.33 (AGND), U1.38 (GND), U2.3 (GND), U2.8 (GND), U2.13 (GND), U2.18 (GND), U2.23 (GND), U2.28 (GND), U2.33 (AGND), U2.38 (GND)
GP0: U1.1 (GPIO0)
GP0_2: J2.5, U2.1 (GPIO0)
GP1: U1.2 (GPIO1)
GP1_2: J2.6, U2.2 (GPIO1)
GP2: U1.4 (GPIO2)
GP2_2: J2.7, U2.4 (GPIO2)
GP3: U1.5 (GPIO3)
GP3_2: J3.5, U2.5 (GPIO3)
GP4: U1.6 (GPIO4)
GP4_2: J3.6, U2.6 (GPIO4)
GP5: U1.7 (GPIO5)
GP5_2: J3.7, U2.7 (GPIO5)
GP6: U1.9 (GPIO6)
GP6_2: SW1.1, U2.9 (GPIO6)
GP7: U1.10 (GPIO7)
GP7_2: SW2.1, U2.10 (GPIO7)
GP8: J5.3, U1.11 (GPIO8)
GP8_2: J2.4, J3.4, U2.11 (GPIO8)
GP9: J4.3, U1.12 (GPIO9)
GP9_2: SW3.1, U2.12 (GPIO9)
GP10: J4.6, J5.6, U1.14 (GPIO10)
GP10_2: J2.2, J3.2, U2.14 (GPIO10)
GP11: J4.5, J5.5, U1.15 (GPIO11)
GP11_2: J2.3, J3.3, U2.15 (GPIO11)
GP12: J4.4, J5.4, U1.16 (GPIO12)
GP12_2: SW4.1, U2.16 (GPIO12)
GP13: J4.7, U1.17 (GPIO13)
GP13_2: SW5.1, U2.17 (GPIO13)
GP14: J5.7, U1.19 (GPIO14)
GP14_2: U2.19 (GPIO14)
GP15: U1.20 (GPIO15)
GP15_2: U2.20 (GPIO15)
GP16: U1.21 (GPIO16), U2.25 (GPIO19)
GP17: U1.22 (GPIO17), U2.22 (GPIO17)
GP18: U1.24 (GPIO18), U2.24 (GPIO18)
GP19: U1.25 (GPIO19), U2.21 (GPIO16)
GP20: U1.26 (GPIO20)
GP20_2: U2.26 (GPIO20)
GP21: U1.27 (GPIO21)
GP22: U1.29 (GPIO22)
GP26: U1.31 (GPIO26_ADC0)
GP27: U1.32 (GPIO27_ADC1)
GP27_2: U2.32 (GPIO27_ADC1)
GP28: U1.34 (GPIO28_ADC2)
GP28_2: U2.34 (GPIO28_ADC2)

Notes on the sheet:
SPI interface (GP16 GP19 invertiti)

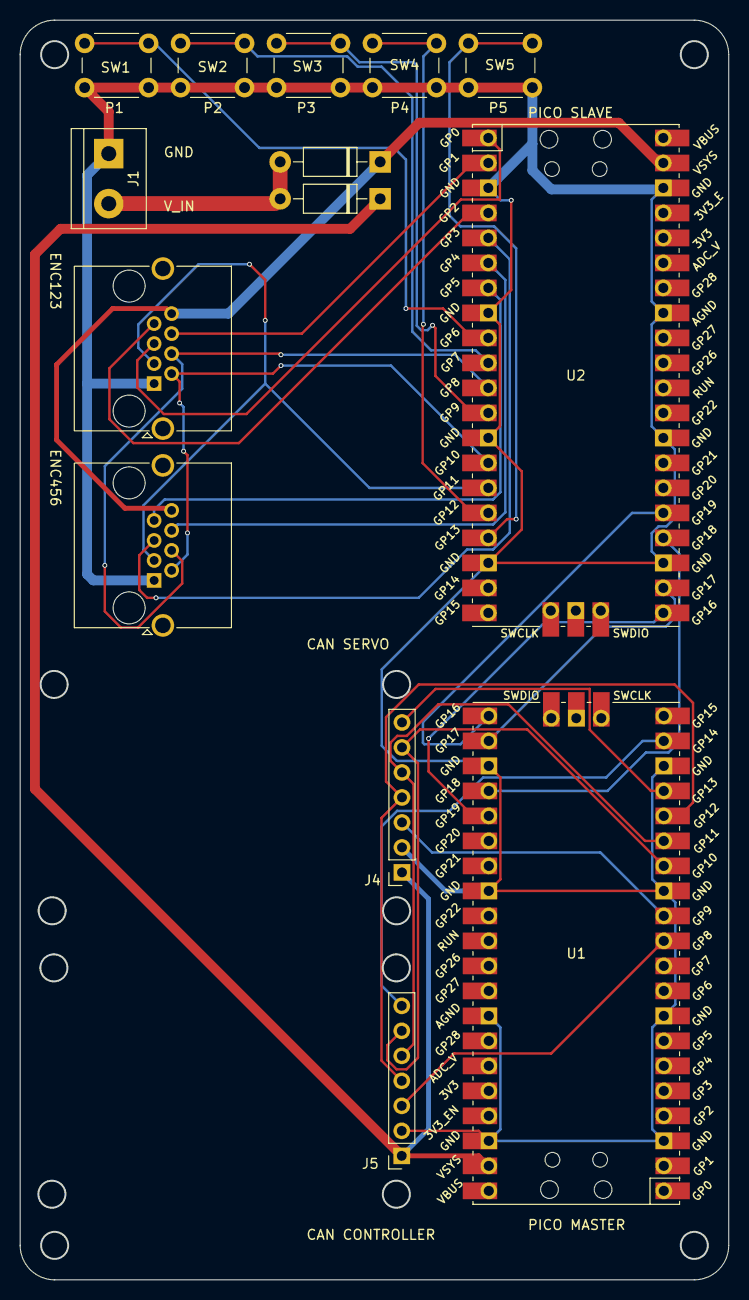
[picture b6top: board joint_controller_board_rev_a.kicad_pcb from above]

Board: 2 copper layers, 72.0 x 128.0 mm, 14 parts (0 on the bottom side), 29 nets.
